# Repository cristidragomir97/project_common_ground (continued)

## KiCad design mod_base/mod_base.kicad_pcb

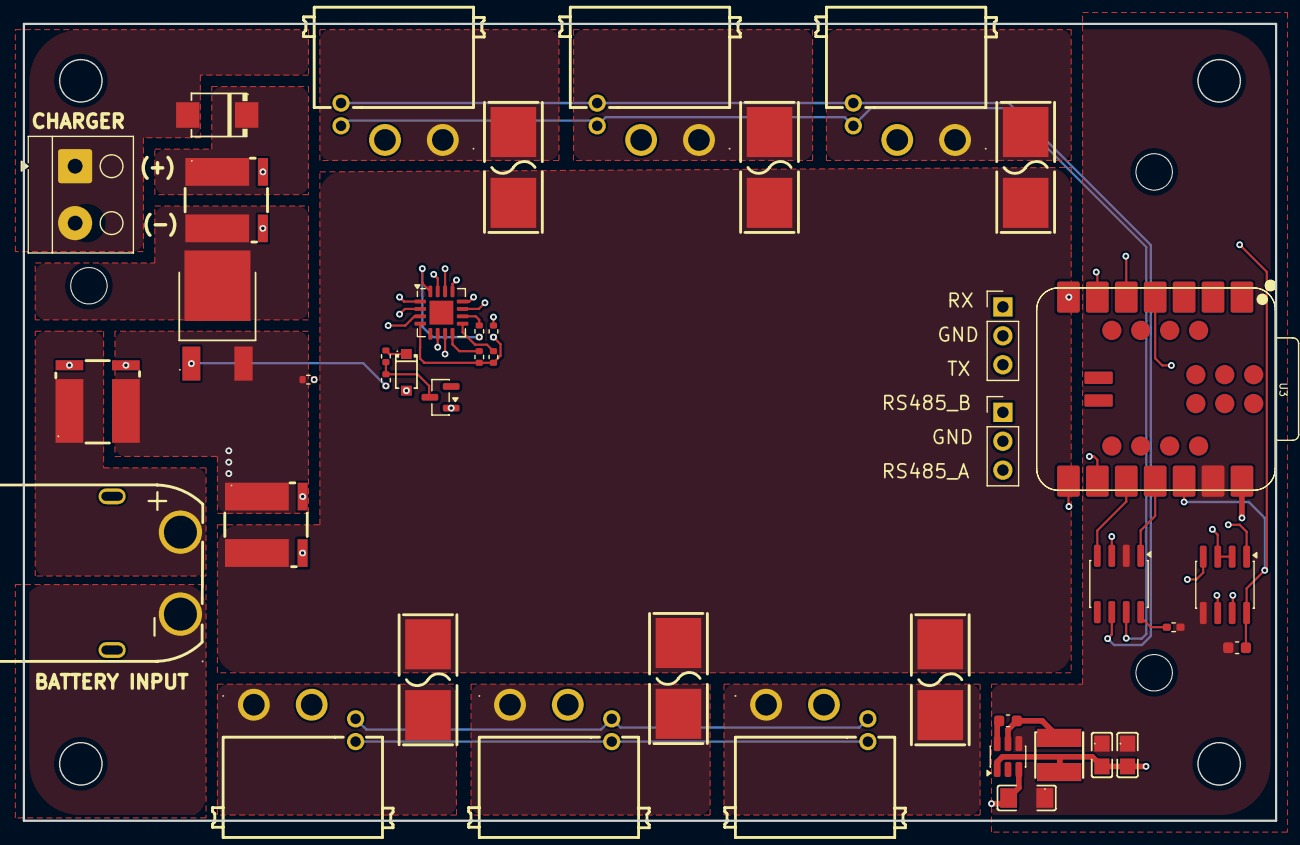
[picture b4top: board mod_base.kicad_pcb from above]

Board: 4 copper layers, 110.0 x 70.0 mm, 42 parts (0 on the bottom side), 45 nets.

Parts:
C4, C6: TCC0805X5R226M100FT; C0805
C5: CL31B106KBHNNNE; C1206
CN1: XT60PW-M; CONN-TH_XT60PW-M
Cboot2: 100nF; C_0603_1608Metric
Cfilt2: 100nF; C_0603_1608Metric
D105: BZT52C12-TP; SOD-123_L2.7-W1.6-LS3.7-RD-A
F2, F3, F4, F5, F6, F7: 0154004.DR; FUSE-SMD_L9.8-W5.1
J1, J2: Conn_01x03_Pin; PinHeader_1x03_P2.54mm_Vertical
J4: Screw_Terminal_01x02; Altech_AK100_1x02_P5.00mm
L2: FNR4030S4R7MT; IND-SMD_L4.0-W4.0_FNR40XXS
Q101: BSS138; SOT-23
Q102: IPD90P04P4L-04-VB; TO-252-2_L6.6-W6.1-P4.57-LS9.9-BR-CW
R1_G102: 10; R_0402_1005Metric
R5, R6, R7: WSLP2726L5000FEA; RES-SMD_4P-L6.9-W6.6_WSLP2726L5000FEA
R9: 10k; R_0402_1005Metric_Pad0.72x0.64mm_HandSolder
R102, R103, R104, R105: 10K; R_0402_1005Metric
R_MOT_EN101: 100k; R_0402_1005Metric
R_MOT_PU101: 100k; R_0402_1005Metric
U1, U2, U5, U6, U8, U9: XT30; CONN-TH_4P-XT30PW-M
U3: XIAO-RA4M1-SMD; XIAO-R4-SMD
U4: SS54_C5200096; SMB_L4.3-W3.6-LS5.4-RD
U7: SN65HVD230; SOIC-8_3.9x4.9mm_P1.27mm
U10: AP63205WU; TSOT-23-6
U11: SP3485EN; SOIC-8_3.9x4.9mm_P1.27mm
U103: INA3221; Texas_RGV0016A_VQFN-16-1EP_4x4mm_P0.65mm_EP2.1x2.1mm

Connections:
+3V3: Cfilt2.1, R103.1, R104.1, R105.1, U3.12 (3V3_OUT), U7.3 (VCC), U11.8 (VCC), U103.4 (VS)
/+5V: C4.2, C6.2, L2.2, U3.14 (VBUS), U10.1 (FB)
/CANH: U1.3, U2.3, U5.3, U6.3, U7.7 (CANH), U8.3, U9.3
/CANL: U1.4, U2.4, U5.4, U6.4, U7.6 (CANL), U8.4, U9.4
/CAN_RX: U3.10 (D9), U7.4 (R)
/CAN_TX: U3.11 (D10), U7.1 (D)
/CUR_BAT+: R6.4, U103.15 (IN+2)
/CUR_BAT-: R6.3, U103.14 (IN-2)
/CUR_DOCK+: R5.4, U103.12 (IN+1)
/CUR_DOCK-: R5.3, U103.11 (IN-1)
/CUR_LOAD+: R7.4, U103.2 (IN+3)
/CUR_LOAD-: R7.3, U103.1 (IN-3)
/DOCK: Q102.2 (D), R5.2
/KILL: Q101.1 (G), U3.9 (D8)
/PWR: F2.1, F3.1, F4.1, F5.1, F6.1, F7.1, R7.2
/RS485_A: J1.3, U11.6 (A)
/RS485_B: J1.1, U11.7 (B)
/RS_EN: U3.4 (D3), U11.2 (~RE), U11.3 (DE)
/RX: J2.1, U3.7 (D6), U11.1 (RO)
/SCL: U3.6 (D5), U103.6 (SCL)
/SDA: U3.5 (D4), U103.7 (SDA)
/TX: J2.3, U3.8 (D7), U11.4 (DI)
/VSYS: C5.2, Q102.3 (S), R6.2, R7.1, R_MOT_PU101.1, U10.3 (IN)
GND: C4.1, C5.1, C6.1, CN1.1 (-), Cfilt2.2, J1.2, J2.2, J4.2, Q101.2 (S), R9.2, U1.2, U2.2, U3.13 (GND), U5.2, U6.2, U7.2 (GND), U8.2, U9.2, U10.4 (GND), U11.5 (GND), U103.3 (GND)
unnamed: CN1.2 (+), R6.1
unnamed: R5.1, U4.1
unnamed: D105.2 (A), R_MOT_PU101.2
unnamed: D105.1 (K), R_MOT_EN101.1
unnamed: F2.2, U2.1
unnamed: F3.2, U6.1
unnamed: F4.2, U1.1
unnamed: F5.2, U8.1
unnamed: F6.2, U5.1
unnamed: F7.2, U9.1
unnamed: J4.1, U4.2
unnamed: Q101.3 (D), R1_G102.2, R_MOT_EN101.2
unnamed: Q102.1 (G), R1_G102.1
unnamed: R9.1, U7.8 (Rs)
unnamed: Cboot2.2, U10.6 (BST)
unnamed: Cboot2.1, L2.1, U10.5 (SW)
unnamed: R103.2, U103.9 (CRITICAL)
unnamed: R102.2, U103.10 (PV)
unnamed: R105.2, U103.13 (TC)
unnamed: R102.1, U103.16 (VPU)
unnamed: R104.2, U103.8 (WARNING)
